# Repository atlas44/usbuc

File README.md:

# usbuc
A PIC32 based modchip for the Nintendo Switch.

## Description
This is an experimental WIP modchip designed to fit inside of the Switch that will trigger [Fusee Gelee](https://github.com/reswitched/fusee-launcher) automatically on boot to launch an arbitrary payload. Installing it requires soldering 5 wires.

## Pictures

## Disclaimer
This is a work-in-process, extremely experimental, and has only had limited testing! If you are not comfortable with small soldering and both software and hardware debugging you should not use this! Mistakes can easily result in a permanently damaged Switch!

## Installation Instructions
TODO

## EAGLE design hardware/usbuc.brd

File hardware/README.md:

# Hardware

## Parts List

### Somewhat Specific parts
| Quantity | Part  | Description | Cost for 1 | Link
| -------- | ----- | ----------- | ---------- | ----
| 1 | PIC32MX270F256B-I/ML | Microcontroller | $3.99 | [DigiKey](https://www.digikey.com/product-detail/en/microchip-technology/PIC32MX270F256B-I-ML/PIC32MX270F256B-I-ML-ND/4902628)
| 1 | NCP551SN | Voltage Regulator | $0.57 | [DigiKey](https://www.digikey.com/product-detail/en/on-semiconductor/NCP551SN33T1G/NCP551SN33T1GOSCT-ND)
| 1 | AT25SF081-XMHD-T | Flash Storage (OPTIONAL! Gives extra space for more payloads) | $0.71 | [DigiKey](https://www.digikey.com/product-detail/en/adesto-technologies/AT25SF081-XMHD-T/1265-1277-1-ND/6827525)

### Easily Substitutable parts
| Quantity | Part  | Description | Cost for 1 | Link
| -------- | ----- | ----------- | ---------- | ----
| 1 | 8.000 MHz Crystal, 5x3.2 | Crystal Oscillator | $0.69 | [DigiKey](https://www.digikey.com/product-detail/en/abracon-llc/ABM3B-8.000MHZ-10-1-U-T/535-9721-1-ND/1873255)
| 2 | 18pF Capacitor 0603 | Capacitors for crystal | $0.10 | [DigiKey](https://www.digikey.com/product-detail/en/yageo/CC0603GRNPO9BN180/311-3922-1-ND/8025011)
| 2 | 1uF Capacitor 0603 | Decoupling capacitors | $0.10 | [DigiKey](https://www.digikey.com/product-detail/en/samsung-electro-mechanics/CL10A105KQ8NNNC/1276-1036-1-ND/3889122)
| 1 | 10uF Capacitor 0603 | Capacitor for microcontroller's internal regulator | $0.21 | [DigiKey](https://www.digikey.com/product-detail/en/tdk-corporation/C1608X5R0J106M080AB/445-4112-1-ND/1975462)
| 1 | 10K Resistor 0603 | Reset pull-up | $0.10 | [DigiKey](https://www.digikey.com/product-detail/en/stackpole-electronics-inc/RMCF0603JG10K0/RMCF0603JG10K0CT-ND/4425128)
| 1 | Green LED 0603 | Indicator LED (OPTIONAL) | $0.27 | [DigiKey](https://www.digikey.com/product-detail/en/lite-on-inc/LTST-S270KGKT/160-1478-1-ND/386892)
| 1 | 330 Resistor 0603 | Resistor for LED (OPTIONAL) | $0.10 | [DigiKey](https://www.digikey.com/product-detail/en/stackpole-electronics-inc/RMCF0603JT330R/RMCF0603JT330RCT-ND/1943164)

Cost per unit with all optional parts, excluding PCB, @1: $7.04

Cost per unit with all optional parts, excluding PCB, @100: $5.6213

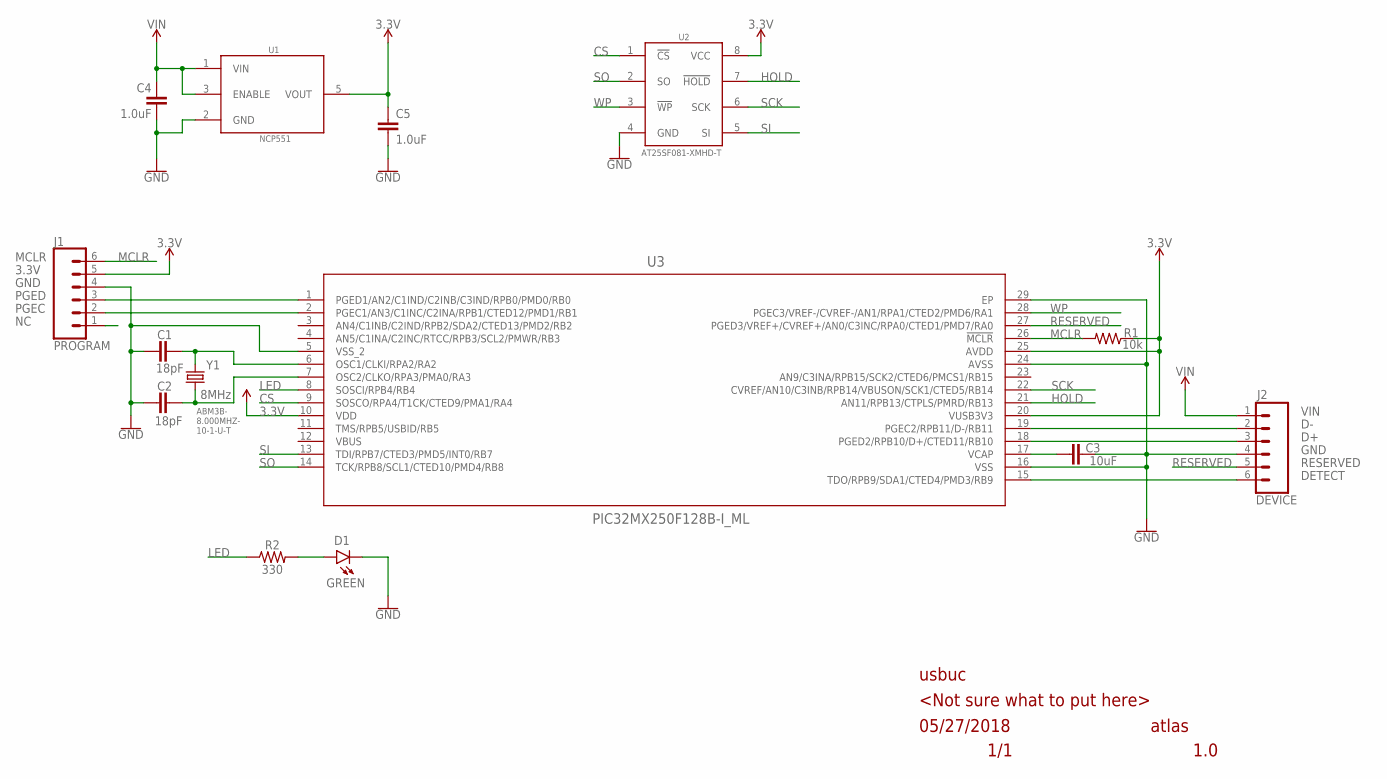
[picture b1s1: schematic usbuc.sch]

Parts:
C1, C2: 18pF; 0603
C3: 10uF; 0603
C4, C5: 1.0uF; 0603
D1: GREEN; LED-0603
J1: PROGRAM; 1X06_FEMALE_LOCK.010
J2: DEVICE; 1X06_LONGPADS
R1: 10k; 0603
R2: 330; 0603
U1: NCP551; TSOP-5
U2: AT25SF081-XMHD-T; TSSOP8
U3: PIC32MX250F128B-I_ML; QFN28_6X6MC
Y1: 8MHz; CRYSTAL-SMD-5X3.2-4PAD

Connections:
3.3V: C5.1, J1.5, R1.1, U1.5 (VOUT), U2.8 (VCC), U3.10 (VDD), U3.20 (VUSB3V3), U3.25 (AVDD)
CS: U2.1 (!CS), U3.9 (SOSCO/RPA4/T1CK/CTED9/PMA1/RA4)
D+: J2.3, U3.18 (PGED2/RPB10/D+/CTED11/RB10)
D-: J2.2, U3.19 (PGEC2/RPB11/D-/RB11)
DETECT: J2.6, U3.15 (TDO/RPB9/SDA1/CTED4/PMD3/RB9)
GND: C1.1, C2.1, C3.2, C4.2, C5.2, D1.C, J1.4, J2.4, U1.2 (GND), U2.4 (GND), U3.5 (VSS_2), U3.16 (VSS), U3.24 (AVSS), U3.29 (EP)
HOLD: U2.7 (!HOLD), U3.21 (AN11/RPB13/CTPLS/PMRD/RB13)
LED: R2.1, U3.8 (SOSCI/RPB4/RB4)
MCLR: J1.6, R1.2, U3.26 (!MCLR)
unnamed: D1.A, R2.2
unnamed: C1.2, U3.6 (OSC1/CLKI/RPA2/RA2), Y1.3 (2)
unnamed: C2.2, U3.7 (OSC2/CLKO/RPA3/PMA0/RA3), Y1.1
unnamed: C3.1, U3.17 (VCAP)
NC: J1.1
PGEC: J1.2, U3.2 (PGEC1/AN3/C1INC/C2INA/RPB1/CTED12/PMD1/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)
PGED: J1.3, U3.1 (PGED1/AN2/C1IND/C2INB/C3IND/RPB0/PMD0/R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)
RESERVED: J2.5, U3.27 (PGED3/VREF+/CVREF+/AN0/C3INC/RPA0/CTED1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)
SCK: U2.6 (SCK), U3.22 (CVREF/AN10/C3INB/RPB14/VBUSON/SCK1/CTED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)
SI: U2.5 (SI), U3.13 (TDI/RPB7/CTED3/PMD5/INT0/RB7)
SO: U2.2 (SO), U3.14 (TCK/RPB8/SCL1/CTED10/PMD4/RB8)
VBUS: U3.12 (VBUS)
VIN: C4.1, J2.1, U1.1 (VIN), U1.3 (ENABLE)
WP: U2.3 (!WP), U3.28 (PGEC3/VREF-/CVREF-/AN1/RPA1/CTED2/PMD6/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)

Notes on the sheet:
usbuc
<Not sure what to put here>
05/27/2018
atlas
1/1
1.0
ABM3B- 8.000MHZ- 10-1-U-T

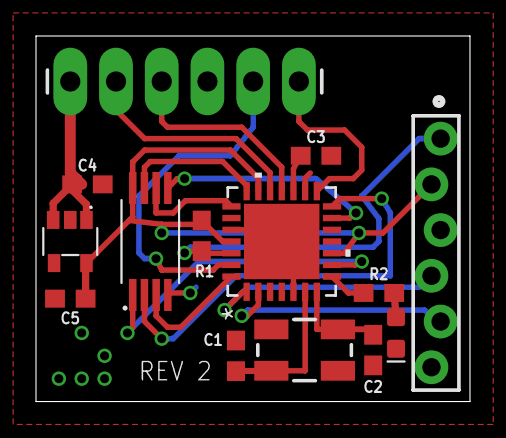
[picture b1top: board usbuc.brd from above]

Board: 2 copper layers, 24.1 x 20.3 mm, 15 parts (0 on the bottom side), 21 nets.

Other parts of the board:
FRAME1: FRAME-A4L; DUMMY

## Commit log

2018-05-27 Clear up crystal values in schematic

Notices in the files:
parts and their libraries:
SparkFun-Clocks: Licensing: Creative Commons ShareAlike 4.0 International - https://creativecommons.org/licenses/by-sa/4.0
